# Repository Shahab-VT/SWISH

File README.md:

# SWISH: A shifting-weight interface of simulated hydrodynamics for haptic perception of virtual fluid vessels

Publication

Shahabedin Sagheb, Frank Wencheng Liu, Alireza Bahremand, Assegid Kidane, Robert LiKamWa
SWISH: A Shifting-Weight Interface of Simulated Hydrodynamics for Haptic Perception of Virtual Fluid Vessels
In Proceedings of UIST'19: https://dl.acm.org/doi/10.1145/3332165.3347870

Abstract

Current VR/AR systems are unable to reproduce the physical sensation of fluid vessels, due to the shifting nature of fluid motion. To this end, we introduce SWISH, 
an ungrounded mixed-reality interface, capable of affording the users a realistic haptic sensation of fluid behaviors in vessels.The chief mechanism behind SWISH 
is in the use of virtual reality tracking and motor actuation to actively relocate the center of gravity of a handheld vessel, emulating the moving center of 
gravity of a handheld vessel that contains fluid. In addition to solving challenges related to reliable and efficient motor actuation, our SWISH designs place 
an emphasis on reproducibility, scalability, and availability to the maker culture. Our virtual-to-physical coupling uses Nvidia Flex's Unity integration for 
virtual fluid dynamics with a3D printed augmented vessel containing a motorized mechanical actuation system.To evaluate the effectiveness and perceptual 
efficacy of SWISH, we conduct a user study with 24 participants, 7 vessel actions, and 2 virtual fluid viscosities in a virtual reality environment. 
In all cases, the users on average reported that the SWISH bucket generates accurate tactile sensations for the fluid behavior. This opens the potential for 
multi-modal interactions with programmable fluids in virtual environments for chemistry education, worker training, and immersive entertainment.

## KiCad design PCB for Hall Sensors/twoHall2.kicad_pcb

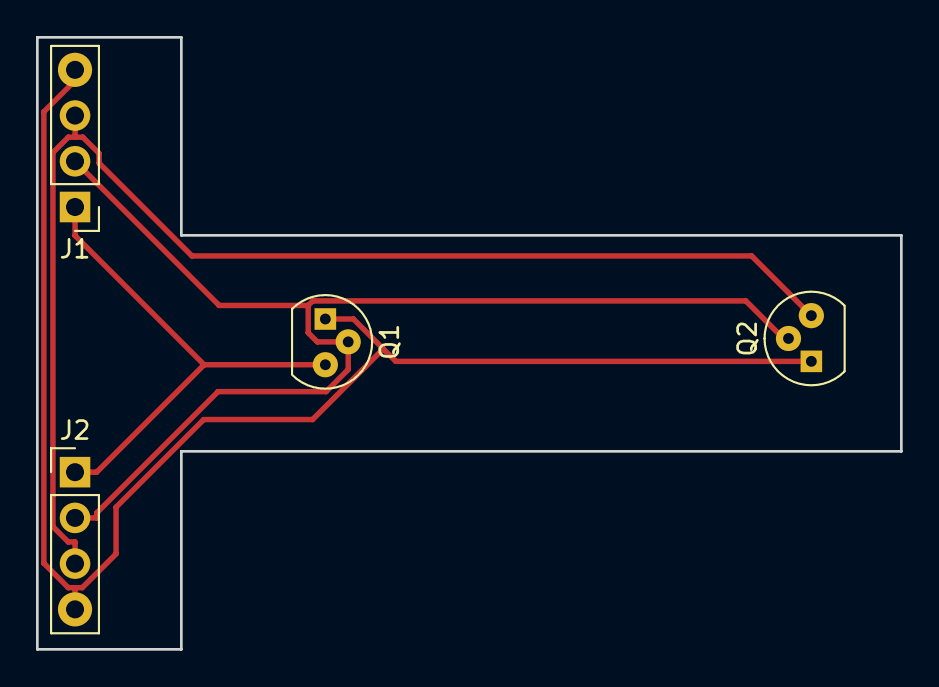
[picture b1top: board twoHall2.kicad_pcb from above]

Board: 2 copper layers, 48.0 x 34.0 mm, 4 parts (0 on the bottom side), 4 nets.

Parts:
J1, J2: Conn_01x04; Pin_Header_Straight_1x04_Pitch2.54mm
Q1, Q2: 2N3904; TO-92_Molded_Narrow

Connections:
unnamed: J1.1, J2.1, Q1.3
unnamed: J1.2, J2.2, Q1.2, Q2.2
unnamed: J1.3, J2.3, Q2.3
unnamed: J1.4, J2.4, Q1.1, Q2.1

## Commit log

2021-09-20 SWISH Design Files Uploaded
2021-09-20 Readme added
2021-09-20 teaser image added
2021-09-20 corrected typo
2021-09-20 BOM uploaded
